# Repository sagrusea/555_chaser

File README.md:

# 555_chaser
A simple 555 led chaser board in the shape of a "spine"
i made this for stasis

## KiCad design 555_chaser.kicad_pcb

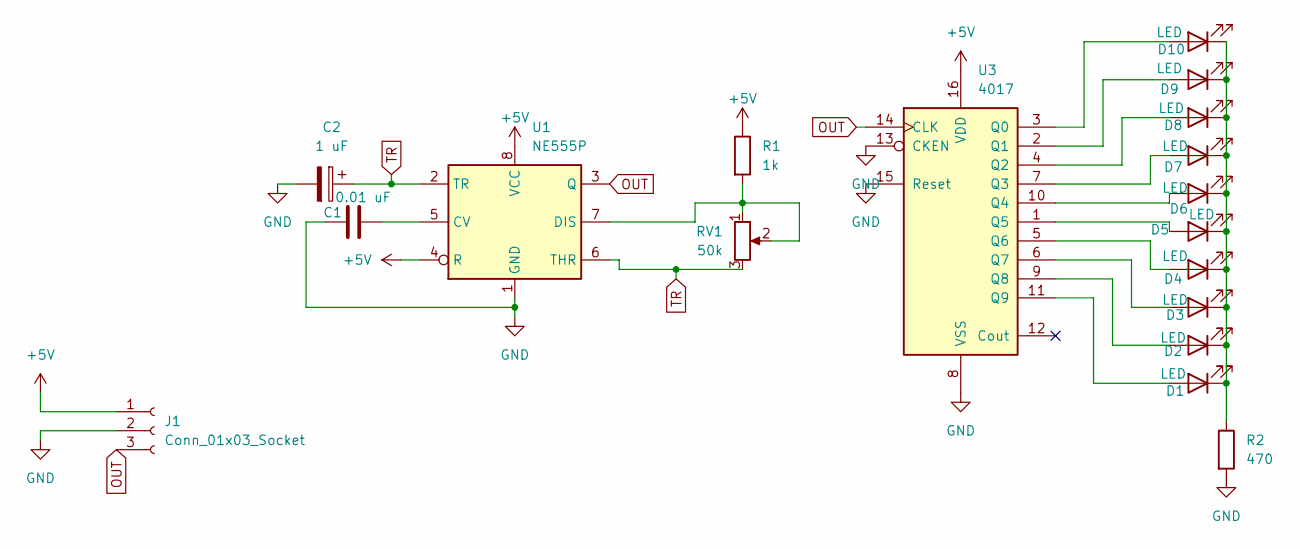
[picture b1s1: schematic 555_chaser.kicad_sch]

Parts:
C1: 0.01 uF; C_Disc_D7.5mm_W2.5mm_P5.00mm
C2: 1 uF; CP_Radial_D5.0mm_P2.00mm
D1, D2, D3, D4, D5, D6, D7, D8, D9, D10: LED; LED_D3.0mm
J1: Conn_01x03_Socket; TerminalBlock_4Ucon_1x03_P3.50mm_Horizontal
R1: 1k; R_Axial_DIN0207_L6.3mm_D2.5mm_P7.62mm_Horizontal
R2: 470; R_Axial_DIN0207_L6.3mm_D2.5mm_P7.62mm_Horizontal
RV1: 50k; Potentiometer_Vishay_T93YA_Vertical
U1: NE555P; DIP-8_W7.62mm
U3: 4017; N16

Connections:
+5V: J1.1, R1.1, U1.4 (R), U1.8 (VCC), U3.16 (VDD)
GND: C1.1, C2.2, J1.2, R2.2, U1.1 (GND), U3.8 (VSS), U3.13 (CKEN), U3.15 (Reset)
unnamed: D1.2 (A), U3.11 (Q9)
unnamed: D1.1 (K), D2.1 (K), D3.1 (K), D4.1 (K), D5.1 (K), D6.1 (K), D7.1 (K), D8.1 (K), D9.1 (K), D10.1 (K), R2.1
unnamed: D2.2 (A), U3.9 (Q8)
unnamed: D3.2 (A), U3.6 (Q7)
unnamed: D4.2 (A), U3.5 (Q6)
unnamed: D5.2 (A), U3.1 (Q5)
unnamed: D6.2 (A), U3.10 (Q4)
unnamed: D7.2 (A), U3.7 (Q3)
unnamed: D8.2 (A), U3.4 (Q2)
unnamed: D9.2 (A), U3.2 (Q1)
unnamed: D10.2 (A), U3.3 (Q0)
unnamed: C1.2, U1.5 (CV)
unnamed: R1.2, RV1.1, RV1.2, U1.7 (DIS)
OUT: J1.3, U1.3 (Q), U3.14 (CLK)
TR: C2.1, RV1.3, U1.2 (TR), U1.6 (THR)

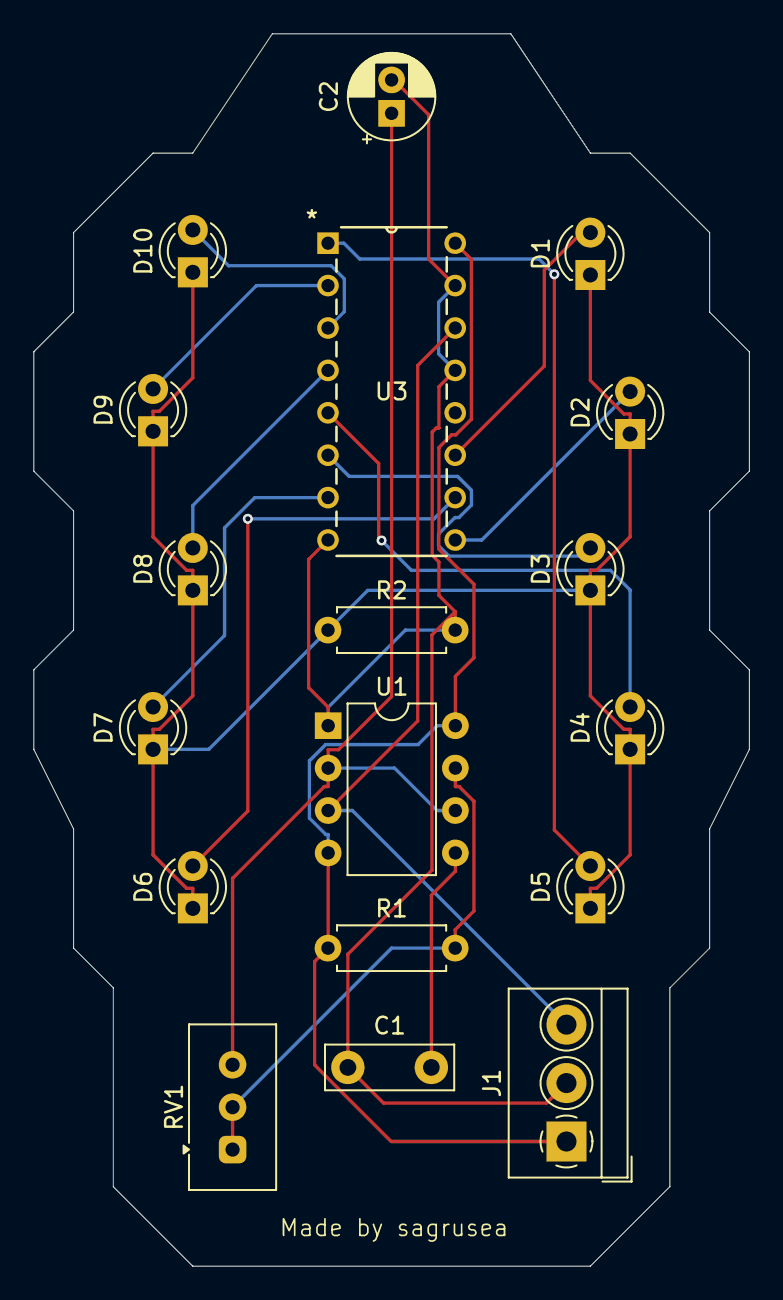
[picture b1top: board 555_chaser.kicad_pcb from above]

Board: 2 copper layers, 42.9 x 73.8 mm, 18 parts (0 on the bottom side), 17 nets.

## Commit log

2026-03-07 Enhance README with project details and image
    Added a description and image for the project.
2026-03-08 Add files via upload
    deleted J2 and made the J1 a 3 block terminal; width 3.5mm
